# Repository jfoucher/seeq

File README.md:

# SEEQ

## A RP2040 midi and CV / Gate sequencer

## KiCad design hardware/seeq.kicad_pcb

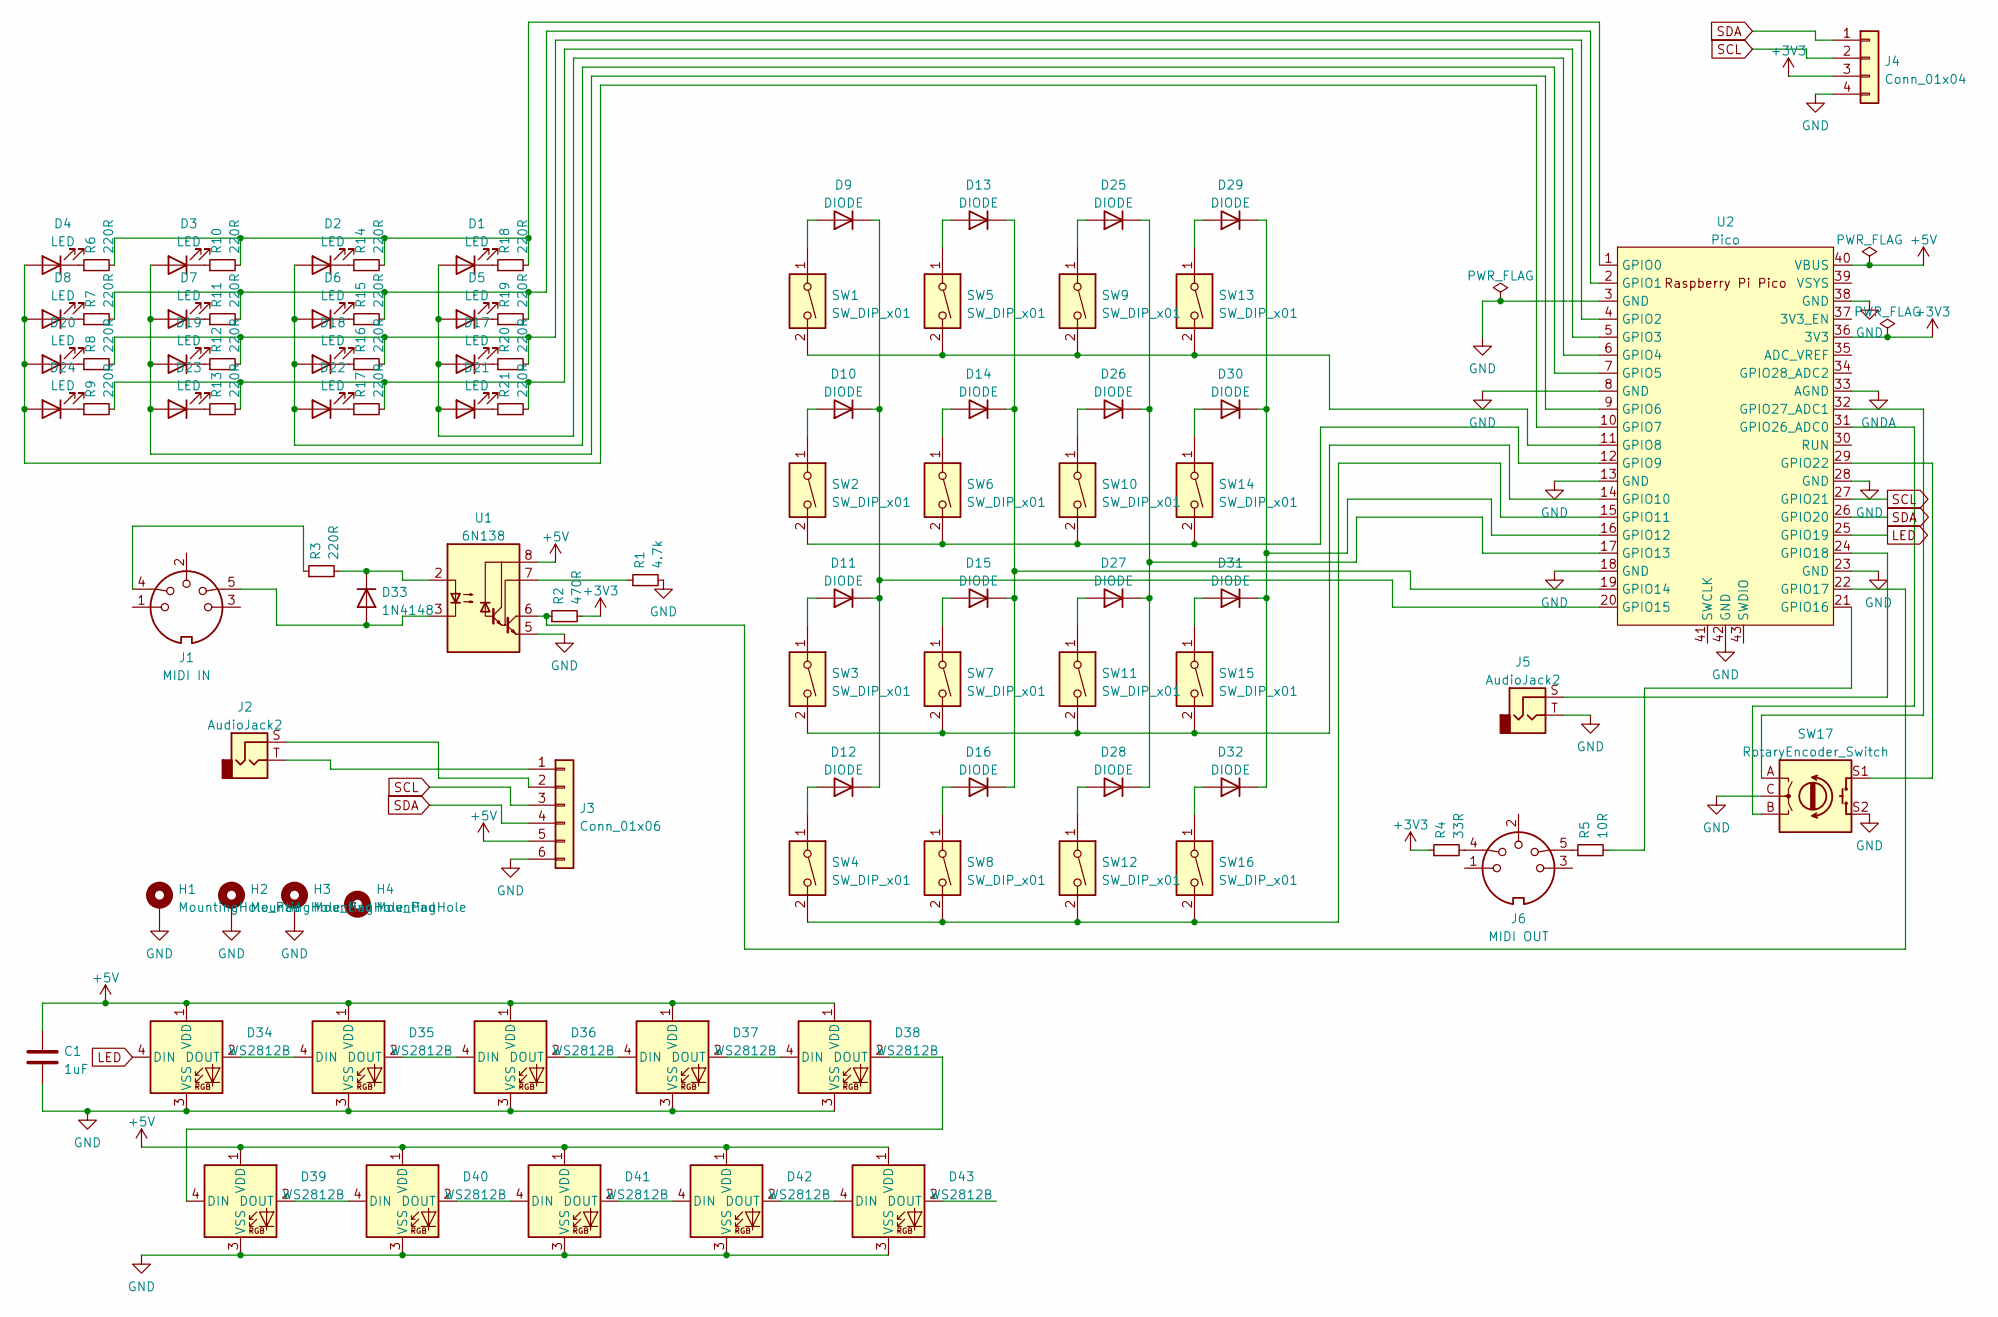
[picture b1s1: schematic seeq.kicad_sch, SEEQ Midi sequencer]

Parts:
C1: 1uF; C_Disc_D5.0mm_W2.5mm_P5.00mm
D1, D2, D3, D4, D5, D6, D7, D8, D17, D18, D19, D20, D21, D22, D23, D24: LED; LED_D5.0mm
D9, D10, D11, D12, D13, D14, D15, D16, D25, D26, D27, D28, D29, D30, D31, D32: DIODE; D_DO-35_SOD27_P7.62mm_Horizontal
D33: 1N4148; D_DO-35_SOD27_P7.62mm_Horizontal
D34, D35, D36, D37, D38, D39, D40, D41, D42, D43: WS2812B; LED_WS2812B_PLCC4_5.0x5.0mm_P3.2mm
H1, H2, H3: MountingHole_Pad; MountingHole_3.2mm_M3_Pad
H4: MountingHole; MountingHole_3.2mm_M3
J1: MIDI IN; din-5
J2, J5: AudioJack2; TRRS-PJ-320A-no-Fmask
J3: Conn_01x06; PinSocket_1x06_P2.54mm_Vertical
J4: Conn_01x04; PinSocket_1x04_P2.54mm_Vertical
J6: MIDI OUT; din-5
R1: 4.7k; R_Axial_DIN0207_L6.3mm_D2.5mm_P10.16mm_Horizontal
R2: 470R; R_Axial_DIN0207_L6.3mm_D2.5mm_P10.16mm_Horizontal
R3, R6, R7, R8, R9, R10, R11, R12, R13, R14, R15, R16, R17, R18, R19, R20, R21: 220R; R_Axial_DIN0207_L6.3mm_D2.5mm_P10.16mm_Horizontal
R4: 33R; R_Axial_DIN0207_L6.3mm_D2.5mm_P10.16mm_Horizontal
R5: 10R; R_Axial_DIN0207_L6.3mm_D2.5mm_P10.16mm_Horizontal
SW1, SW2, SW3, SW4, SW5, SW6, SW7, SW8, SW9, SW10, SW11, SW12, SW13, SW14, SW15, SW16: SW_DIP_x01; SW_Cherry_MX_PCB_1.00u
SW17: RotaryEncoder_Switch; RotaryEncoder_Alps_EC11E-Switch_Vertical_H20mm
U1: 6N138; DIP-8_W7.62mm
U2: Pico; RPi_Pico_SMD_TH

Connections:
+3V3: J4.3, R2.2, R4.1, U2.36 (3V3)
+5V: C1.1, D34.1 (VDD), D35.1 (VDD), D36.1 (VDD), D37.1 (VDD), D38.1 (VDD), D39.1 (VDD), D40.1 (VDD), D41.1 (VDD), D42.1 (VDD), D43.1 (VDD), J3.5, U1.8 (VCC), U2.40 (VBUS)
GND: C1.2, D34.3 (VSS), D35.3 (VSS), D36.3 (VSS), D37.3 (VSS), D38.3 (VSS), D39.3 (VSS), D40.3 (VSS), D41.3 (VSS), D42.3 (VSS), D43.3 (VSS), H1.1, H2.1, H3.1, J3.6, J4.4, J5.T, R1.2, SW17.C, SW17.S2, U1.5 (GND), U2.3 (GND), U2.8 (GND), U2.13 (GND), U2.18 (GND), U2.23 (GND), U2.28 (GND), U2.38 (GND), U2.42 (GND)
GNDA: U2.33 (AGND)
LED: D34.4 (DIN), U2.25 (GPIO19)
unnamed: D1.1 (K), R18.1
unnamed: D1.2 (A), D5.2 (A), D17.2 (A), D21.2 (A), U2.6 (GPIO4)
unnamed: D2.1 (K), R14.1
unnamed: D3.1 (K), R10.1
unnamed: D4.1 (K), R6.1
unnamed: D5.1 (K), R19.1
unnamed: D6.1 (K), R15.1
unnamed: D7.1 (K), R11.1
unnamed: D8.1 (K), R7.1
unnamed: D9.2 (A), SW1.1
unnamed: D9.1 (K), D10.1 (K), D11.1 (K), D12.1 (K), U2.20 (GPIO15)
unnamed: D10.2 (A), SW2.1
unnamed: D11.2 (A), SW3.1
unnamed: D12.2 (A), SW4.1
unnamed: D13.1 (K), D14.1 (K), D15.1 (K), D16.1 (K), U2.19 (GPIO14)
unnamed: D13.2 (A), SW5.1
unnamed: D14.2 (A), SW6.1
unnamed: D15.2 (A), SW7.1
unnamed: D16.2 (A), SW8.1
unnamed: D17.1 (K), R20.1
unnamed: D18.1 (K), R16.1
unnamed: D2.2 (A), D6.2 (A), D18.2 (A), D22.2 (A), U2.7 (GPIO5)
unnamed: D19.1 (K), R12.1
unnamed: D3.2 (A), D7.2 (A), D19.2 (A), D23.2 (A), U2.9 (GPIO6)
unnamed: D20.1 (K), R8.1
unnamed: D4.2 (A), D8.2 (A), D20.2 (A), D24.2 (A), U2.10 (GPIO7)
unnamed: D21.1 (K), R21.1
unnamed: D22.1 (K), R17.1
unnamed: D23.1 (K), R13.1
unnamed: D24.1 (K), R9.1
unnamed: D25.1 (K), D26.1 (K), D27.1 (K), D28.1 (K), U2.17 (GPIO13)
unnamed: D25.2 (A), SW9.1
unnamed: D26.2 (A), SW10.1
unnamed: D27.2 (A), SW11.1
unnamed: D28.2 (A), SW12.1
unnamed: D29.1 (K), D30.1 (K), D31.1 (K), D32.1 (K), U2.16 (GPIO12)
unnamed: D29.2 (A), SW13.1
unnamed: D30.2 (A), SW14.1
unnamed: D31.2 (A), SW15.1
unnamed: D32.2 (A), SW16.1
unnamed: D33.1 (K), R3.2, U1.2 (C1)
unnamed: D33.2 (A), J1.5, U1.3 (C2)
unnamed: D34.2 (DOUT), D35.4 (DIN)
unnamed: D35.2 (DOUT), D36.4 (DIN)
unnamed: D36.2 (DOUT), D37.4 (DIN)
unnamed: D37.2 (DOUT), D38.4 (DIN)
unnamed: D38.2 (DOUT), D39.4 (DIN)
unnamed: D39.2 (DOUT), D40.4 (DIN)
unnamed: D40.2 (DOUT), D41.4 (DIN)
unnamed: D41.2 (DOUT), D42.4 (DIN)
unnamed: D42.2 (DOUT), D43.4 (DIN)
unnamed: J1.4, R3.1
unnamed: J2.S, J3.2
unnamed: J2.T, J3.1
unnamed: J5.S, U2.24 (GPIO18)
unnamed: J6.4, R4.2
unnamed: J6.5, R5.1
unnamed: R1.1, U1.7 (VO1)
unnamed: R2.1, U1.6 (VO2), U2.22 (GPIO17)
unnamed: R5.2, U2.21 (GPIO16)
unnamed: R6.2, R10.2, R14.2, R18.2, U2.1 (GPIO0)
unnamed: R7.2, R11.2, R15.2, R19.2, U2.2 (GPIO1)
unnamed: R8.2, R12.2, R16.2, R20.2, U2.4 (GPIO2)
unnamed: R9.2, R13.2, R17.2, R21.2, U2.5 (GPIO3)
unnamed: SW1.2, SW5.2, SW9.2, SW13.2, U2.11 (GPIO8)
unnamed: SW2.2, SW6.2, SW10.2, SW14.2, U2.12 (GPIO9)
unnamed: SW3.2, SW7.2, SW11.2, SW15.2, U2.14 (GPIO10)
unnamed: SW4.2, SW8.2, SW12.2, SW16.2, U2.15 (GPIO11)
unnamed: SW17.A, U2.32 (GPIO27_ADC1)
unnamed: SW17.B, U2.31 (GPIO26_ADC0)
unnamed: SW17.S1, U2.29 (GPIO22)
SCL: J3.3, J4.2, U2.27 (GPIO21)
SDA: J3.4, J4.1, U2.26 (GPIO20)

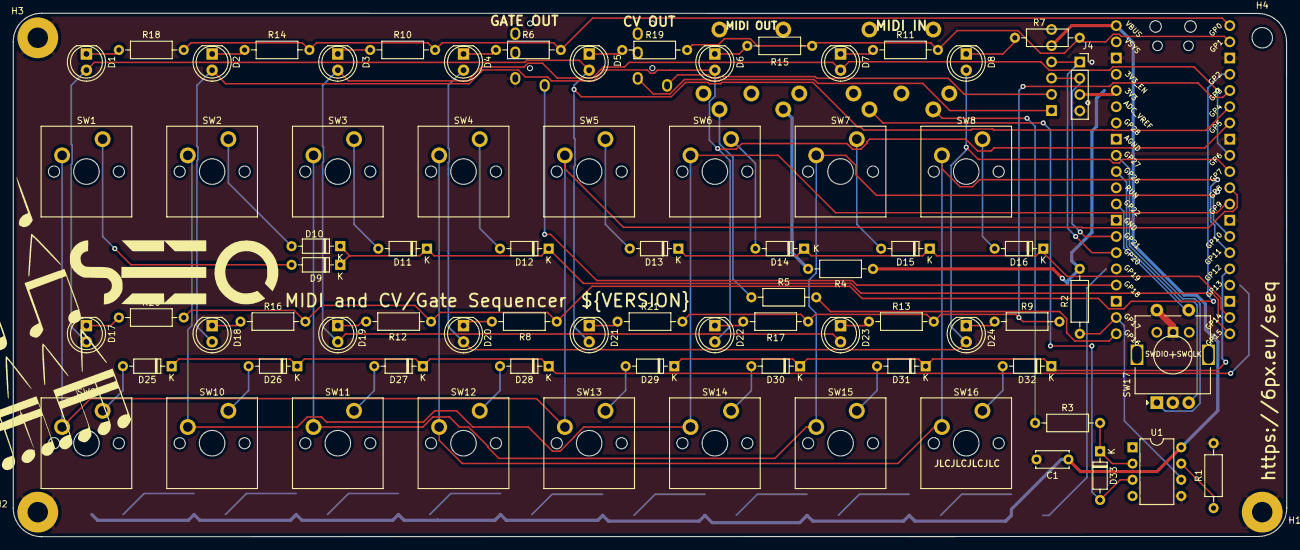
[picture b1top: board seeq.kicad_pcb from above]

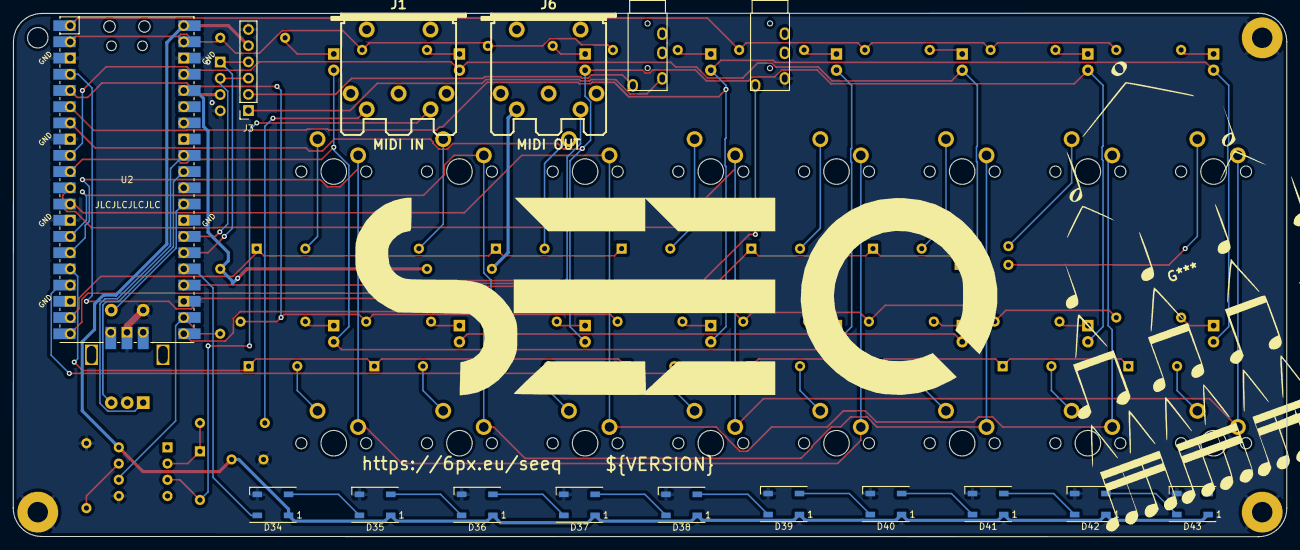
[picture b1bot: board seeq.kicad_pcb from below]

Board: 2 copper layers, 199.5 x 82.0 mm, 94 parts (16 on the bottom side), 77 nets.

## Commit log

2022-12-07 Midi over USB works
2022-12-14 USB CDC and MIDI work at the same time.
2022-12-14 Keypad WIP
2022-12-14 keypad handling works and lights up correct LED
2022-12-15 Save data to flash + Show notes on display.
2022-12-15 Handle WS2812 LED
2022-12-19 change velocity by turning while pressing it and holding down a key
2022-12-26 Can record + start adding hardware
2022-12-28 first prototype board
2022-12-28 ignore backups
2022-12-29 Only save data right after a note was sent.
2022-12-29 Add 3D models
2023-01-25 Update software for PCB + PCB fixes
2023-02-16 Add kibot and docs
2023-02-16 fix erc / drc
2023-02-16 fix docs + add bottom 3D render
2023-02-16 fix images
2023-02-16 try to add 3D fo switches
2023-02-16 stp files
2023-02-16 color
2023-02-16 image
2023-03-25 Add download links.
2023-03-25 links on their own line
2023-03-25 Add jlc order number
2023-03-25 Fix ERC
2023-03-27 Add licenses
2023-03-27 Add license image in footer
